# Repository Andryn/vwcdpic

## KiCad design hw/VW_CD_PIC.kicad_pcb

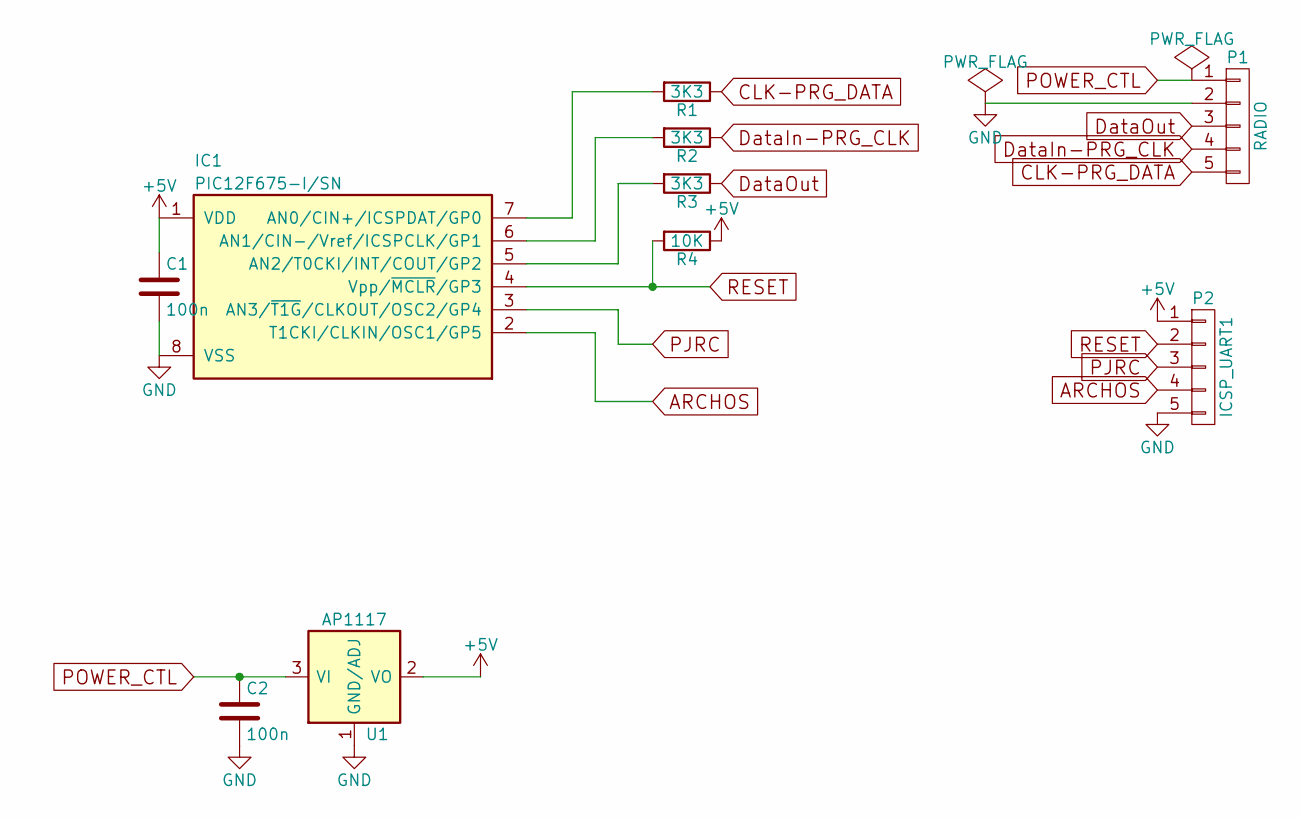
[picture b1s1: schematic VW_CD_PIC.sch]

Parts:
C1, C2: 100n; C_1206_HandSoldering
IC1: PIC12F675-I/SN; C7812
P1: RADIO; Socket_Strip_Straight_1x05
P2: ICSP_UART1; Socket_Strip_Straight_1x05
R1, R2, R3: 3K3; R_1206_HandSoldering
R4: 10K; R_1206_HandSoldering
U1: AP1117; SOT-223

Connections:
+5V: C1.1, IC1.1 (VDD), P2.1, R4.1, U1.2 (VO)
ARCHOS: IC1.2 (T1CKI/CLKIN/OSC1/GP5), P2.4
CLK-PRG_DATA: P1.5, R1.1
DataIn-PRG_CLK: P1.4, R2.1
DataOut: P1.3, R3.1
GND: C1.2, C2.2, IC1.8 (VSS), P1.2, P2.5, U1.1 (GND/ADJ)
unnamed: IC1.5 (AN2/T0CKI/INT/COUT/GP2), R3.2
unnamed: IC1.6 (AN1/CIN-/Vref/ICSPCLK/GP1), R2.2
unnamed: IC1.7 (AN0/CIN+/ICSPDAT/GP0), R1.2
PJRC: IC1.3 (AN3/~T1G~/CLKOUT/OSC2/GP4), P2.3
POWER_CTL: C2.1, P1.1, U1.3 (VI)
RESET: IC1.4 (Vpp/~MCLR~/GP3), P2.2, R4.2

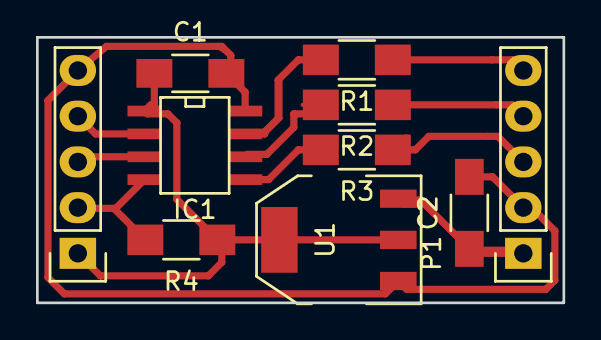
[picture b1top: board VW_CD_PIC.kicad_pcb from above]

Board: 2 copper layers, 29.2 x 14.8 mm, 10 parts (0 on the bottom side), 12 nets.

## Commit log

2016-04-15 Move hw->hw.old
2016-04-15 Add .gitignore
2016-04-15 Redraw diagram and PCB for 1 layout and SMD
